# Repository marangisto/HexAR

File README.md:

# HexAR
Six-way Attack-Release Envelope Generator

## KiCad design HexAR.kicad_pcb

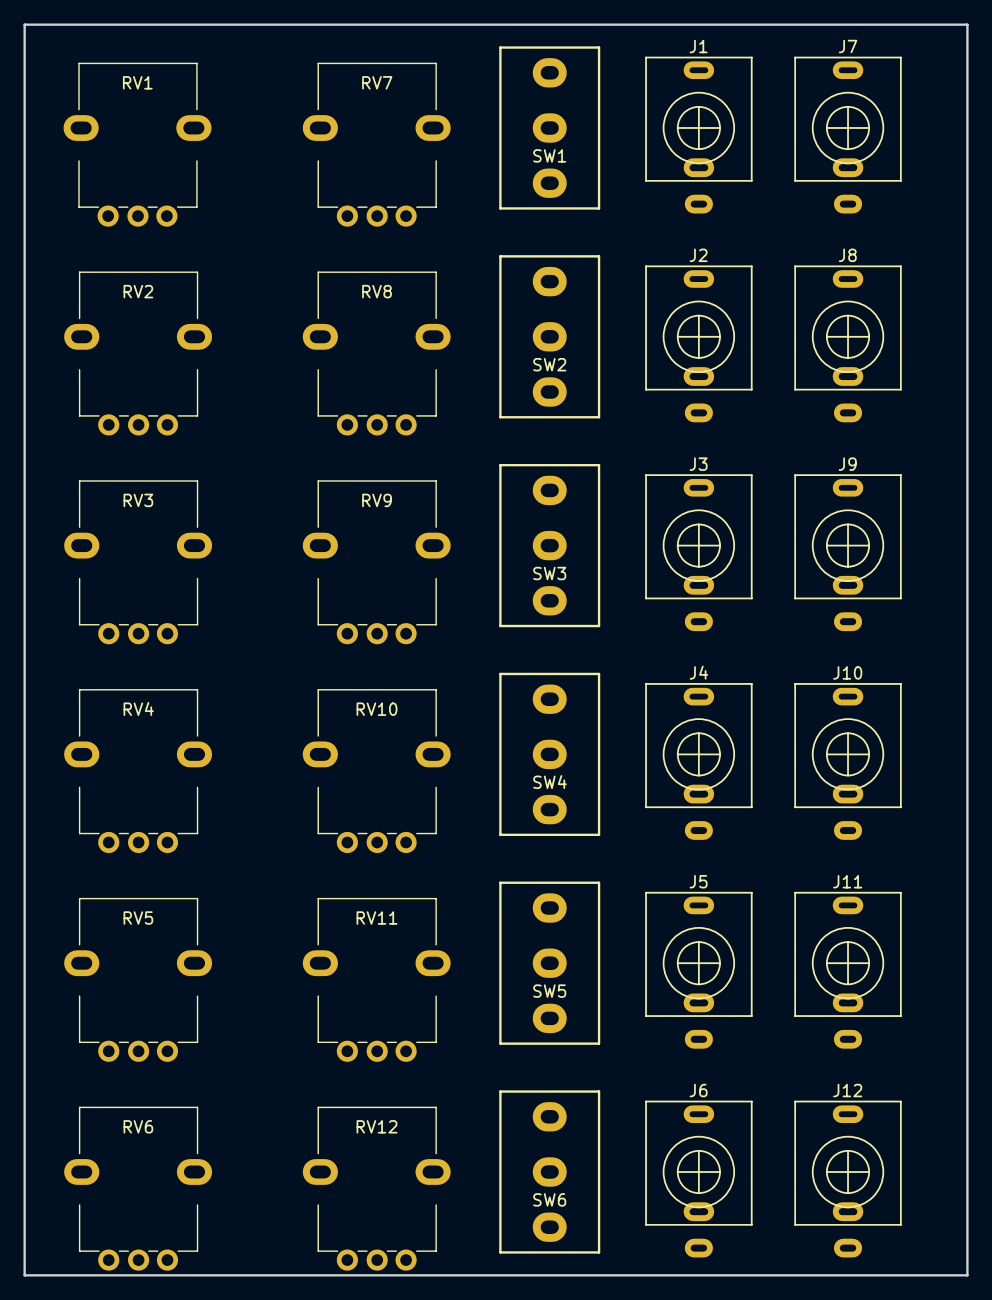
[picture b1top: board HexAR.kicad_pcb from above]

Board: 2 copper layers, 80.3 x 106.5 mm, 30 parts (0 on the bottom side), 2 nets, no tracks yet.

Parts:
J1, J2, J3, J4, J5, J6, J7, J8, J9, J10, J11, J12: AudioJack2_SwitchT; PJ398SM
RV1, RV2, RV3, RV4, RV5, RV6, RV7, RV8, RV9, RV10, RV11, RV12: R_POT; AlpsRK09K
SW1, SW2, SW3, SW4, SW5, SW6: SW_SPDT_MSM; SPDT

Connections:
GND: RV1.3, RV2.3, RV3.3, RV4.3, RV5.3, RV6.3, RV7.3, RV8.3, RV9.3, RV10.3, RV11.3, RV12.3
VCC: RV1.1, RV2.1, RV3.1, RV4.1, RV5.1, RV6.1, RV7.1, RV8.1, RV9.1, RV10.1, RV11.1, RV12.1

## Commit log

2019-04-30 First mechanical design.
